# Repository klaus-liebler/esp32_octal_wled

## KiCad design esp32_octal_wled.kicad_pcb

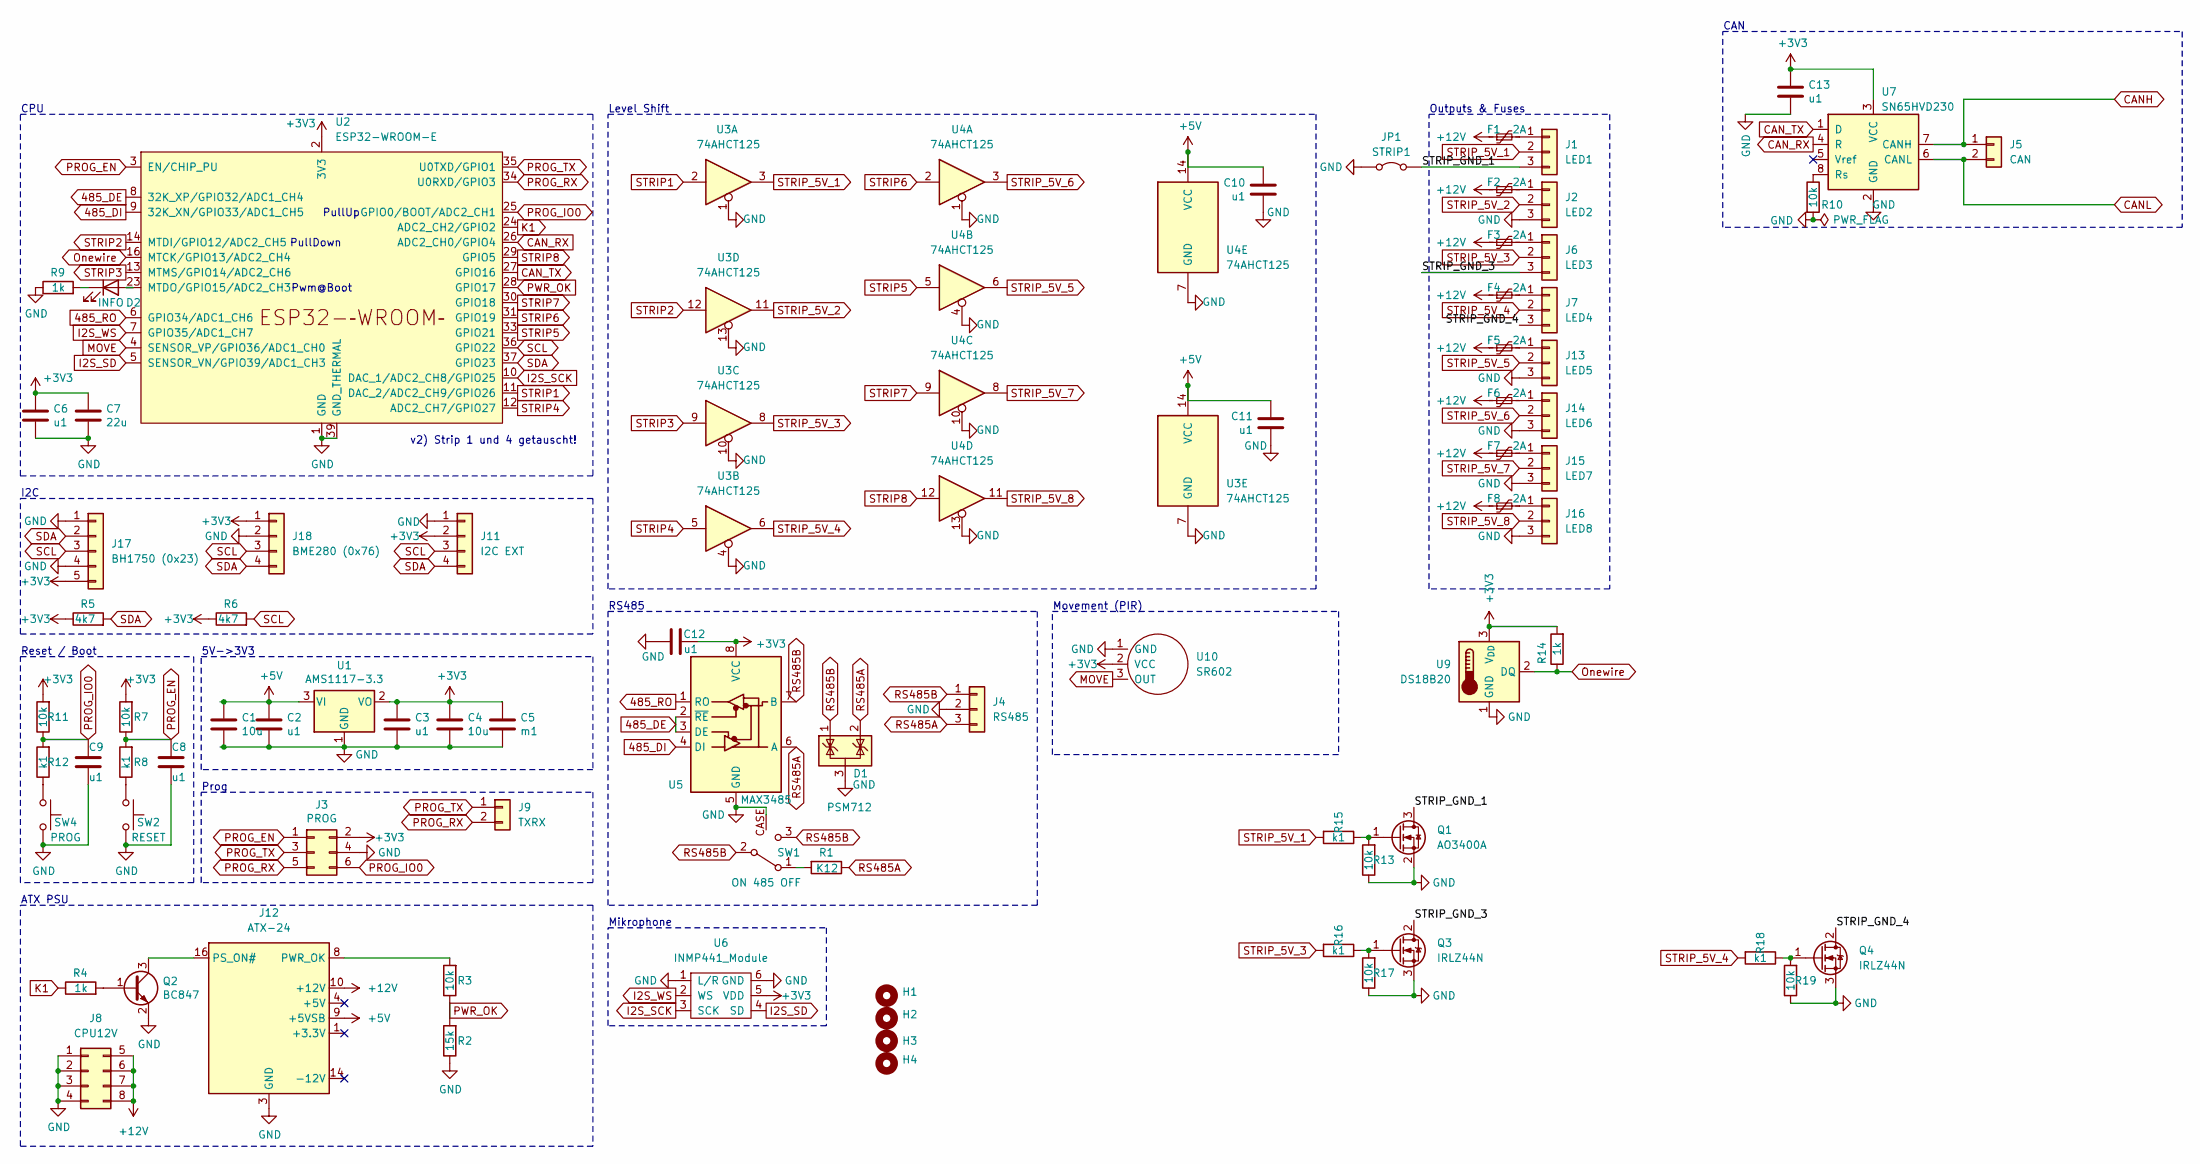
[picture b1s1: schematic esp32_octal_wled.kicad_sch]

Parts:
C1, C4: 10u; C_0805_2012Metric_Pad1.18x1.45mm_HandSolder
C2: u1; C_0805_2012Metric_Pad1.18x1.45mm_HandSolder; JLCPCB C19702
C3, C8, C9, C12, C13: u1; C_0805_2012Metric_Pad1.18x1.45mm_HandSolder
C5: m1; C_1206_3216Metric_Pad1.33x1.80mm_HandSolder; JLCPCB C15008
C6, C10, C11: u1; C_0805_2012Metric_Pad1.18x1.45mm_HandSolder; JLCPCB C1525
C7: 22u; C_0805_2012Metric_Pad1.18x1.45mm_HandSolder; JLCPCB C59461
D1: PSM712; SOT-23_Handsoldering
D2: INFO; LED_0805_2012Metric_Pad1.15x1.40mm_HandSolder
F1, F2, F3, F4, F5, F6, F7, F8: 2A; Fuse_2920_7451Metric_Pad2.10x5.45mm_HandSolder
H1, H2, H3, H4: MountingHole_3.2mm_M3
J1: LED1; PhoenixContact_MC_1,5_3-G-3.5_1x03_P3.50mm_Horizontal_small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
J2: LED2; PhoenixContact_MC_1,5_3-G-3.5_1x03_P3.50mm_Horizontal_small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
J3: PROG; IDC_2x03_P1.27mm_Vertical
J4: RS485; PhoenixContact_MC_1,5_3-G-3.5_1x03_P3.50mm_Horizontal_small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
J5: CAN; PhoenixContact_MCV_1,5_2-G-3.5_1x02_P3.50mm_Vertical
J6: LED3; PhoenixContact_MC_1,5_3-G-3.5_1x03_P3.50mm_Horizontal_small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
J7: LED4; PhoenixContact_MC_1,5_3-G-3.5_1x03_P3.50mm_Horizontal_small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
J8: CPU12V; Molex_Mini-Fit_Jr_5569-08A2_2x04_P4.20mm_Horizontal
J9: TXRX; TestPoint_2Pads_Pitch2.54mm_Drill0.8mm
J11: I2C EXT; JST_XH_S4B-XH-A-1_1x04_P2.50mm_Horizontal_SmallerCourtyard
J12: ATX-24; Molex_Mini-Fit_Jr_5569-24A2_2x12_P4.20mm_Horizontal
J13: LED5; PhoenixContact_MC_1,5_3-G-3.5_1x03_P3.50mm_Horizontal_small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
J14: LED6; PhoenixContact_MC_1,5_3-G-3.5_1x03_P3.50mm_Horizontal_small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
J15: LED7; PhoenixContact_MC_1,5_3-G-3.5_1x03_P3.50mm_Horizontal_small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
J16: LED8; PhoenixContact_MC_1,5_3-G-3.5_1x03_P3.50mm_Horizontal_small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
J17: BH1750 (0x23); PinSocket_1x05_P2.54mm_Vertical
J18: BME280 (0x76); PinSocket_1x04_P2.54mm_Vertical
JP1: STRIP1; SolderJumper-2_P1.3mm_Bridged2Bar_Pad1.0x1.5mm
Q1: AO3400A; SOT-23_Handsoldering
Q2: BC847; SOT-23_Handsoldering
Q3, Q4: IRLZ44N; TO-220-3_Vertical
R1: K12; R_1206_3216Metric_Pad1.30x1.75mm_HandSolder
R2: 15k; R_0805_2012Metric_Pad1.20x1.40mm_HandSolder
R3, R7, R10, R11, R13, R17, R19: 10k; R_0805_2012Metric_Pad1.20x1.40mm_HandSolder
R4, R9, R14: 1k; R_0805_2012Metric_Pad1.20x1.40mm_HandSolder
R5, R6: 4k7; R_0805_2012Metric_Pad1.20x1.40mm_HandSolder
R8, R12, R15, R16, R18: k1; R_0805_2012Metric_Pad1.20x1.40mm_HandSolder
SW1: ON 485 OFF; SW_SPDT_PCM12_handsolder
SW2: RESET; SW_SPST_TL3342_smaller_handsolder
SW4: PROG; SW_SPST_TL3342_smaller_handsolder
U1: AMS1117-3.3; SOT-223-3_TabPin2
U2: ESP32-WROOM-E; ESP32-WROOM-32_HANDSOLDER
U3, U4: 74AHCT125; SOIC-14_3.9x8.7mm_P1.27mm_handsolder
U5: MAX3485; SOIC-8_3.9x4.9mm_P1.27mm_handsolder
U6: INMP441_Module
U7: SN65HVD230; SOIC-8_3.9x4.9mm_P1.27mm_handsolder
U9: DS18B20; TO-92L_HandSolder
U10: SR602; PIR_Sensor_SR602

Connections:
485_DE: U2.8 (32K_XP/GPIO32/ADC1_CH4), U5.2 (~RE), U5.3 (DE)
485_DI: U2.9 (32K_XN/GPIO33/ADC1_CH5), U5.4 (DI)
485_RO: U2.6 (GPIO34/ADC1_CH6), U5.1 (RO)
+3V3: C3.1, C4.1, C5.1, C6.1, C7.1, C12.1, C13.1, J3.2, J11.2, J17.5, J18.1, R5.1, R6.1, R7.2, R11.2, R14.2, U1.2 (VO), U2.2 (3V3), U5.8 (VCC), U6.5 (VDD), U7.3 (VCC), U9.3 (V_{DD}), U10.2 (VCC)
+5V: C1.1, C2.1, C10.1, C11.1, J12.9 (+5VSB), U1.3 (VI), U3.14 (VCC), U4.14 (VCC)
+12V: F1.1, F2.1, F3.1, F4.1, F5.1, F6.1, F7.1, F8.1, J8.5, J8.6, J8.7, J8.8, J12.10 (+12V), J12.11 (+12V)
/STRIP_GND_1: J1.3, JP1.2 (B), Q1.3 (D)
/STRIP_GND_3: J6.3, Q3.2 (D)
/STRIP_GND_4: J7.3, Q4.2 (D)
CANH: J5.1, U7.7 (CANH)
CANL: J5.2, U7.6 (CANL)
CAN_RX: U2.26 (ADC2_CH0/GPIO4), U7.4 (R)
CAN_TX: U2.27 (GPIO16), U7.1 (D)
GND: C1.2, C2.2, C3.2, C4.2, C5.2, C6.2, C7.2, C8.2, C9.2, C10.2, C11.2, C12.2, C13.2, D1.3 (A), J2.3, J3.4, J4.2, J8.1, J8.2, J8.3, J8.4, J11.1, J12.3 (GND), J12.5 (GND), J12.7 (GND), J12.15 (GND), J12.17 (GND), J12.18 (GND), J12.19 (GND), J12.24 (GND), J13.3, J14.3, J15.3, J16.3, J17.1, J17.4, J18.2, JP1.1 (A), Q1.2 (S), Q2.2 (E), Q3.3 (S), Q4.3 (S), R2.1, R9.1, R10.2, R13.1, R17.1, R19.1, SW1.CASE, SW2.2, SW4.2, U1.1 (GND), U2.1 (GND), U2.15 (GND), U2.38 (GND), U2.39 (GND_THERMAL), U3.1, U3.4, U3.7 (GND), U3.10, U3.13, U4.1, U4.4, U4.7 (GND), U4.10, U4.13, U5.5 (GND), U6.1 (L/R), U6.6 (GND), U7.2 (GND), U9.1 (GND), U10.1 (GND)
I2S_SCK: U2.10 (DAC_1/ADC2_CH8/GPIO25), U6.3 (SCK)
I2S_SD: U2.5 (SENSOR_VN/GPIO39/ADC1_CH3), U6.4 (SD)
I2S_WS: U2.7 (GPIO35/ADC1_CH7), U6.2 (WS)
K1: R4.1, U2.24 (ADC2_CH2/GPIO2)
MOVE: U2.4 (SENSOR_VP/GPIO36/ADC1_CH0), U10.3 (OUT)
unnamed: D2.2 (A), U2.23 (MTDO/GPIO15/ADC2_CH3)
unnamed: D2.1 (K), R9.2
unnamed: F1.2, J1.1
unnamed: F2.2, J2.1
unnamed: F3.2, J6.1
unnamed: F4.2, J7.1
unnamed: J12.16 (PS_ON#), Q2.3 (C)
unnamed: J12.8 (PWR_OK), R3.2
unnamed: F5.2, J13.1
unnamed: F6.2, J14.1
unnamed: F7.2, J15.1
unnamed: F8.2, J16.1
unnamed: Q1.1 (G), R13.2, R15.1
unnamed: Q2.1 (B), R4.2
unnamed: Q3.1 (G), R16.1, R17.2
unnamed: Q4.1 (G), R18.1, R19.2
unnamed: R8.1, SW2.1
unnamed: R12.1, SW4.1
unnamed: R1.2, SW1.1 (A)
unnamed: R10.1, U7.8 (Rs)
Onewire: R14.1, U2.16 (MTCK/GPIO13/ADC2_CH4), U9.2 (DQ)
PROG_EN: C8.1, J3.1, R7.1, R8.2, U2.3 (EN/CHIP_PU)
PROG_IO0: C9.1, J3.6, R11.1, R12.2, U2.25 (GPIO0/BOOT/ADC2_CH1)
PROG_RX: J3.5, J9.2, U2.34 (U0RXD/GPIO3)
PROG_TX: J3.3, J9.1, U2.35 (U0TXD/GPIO1)
PWR_OK: R2.2, R3.1, U2.28 (GPIO17)
RS485A: D1.2 (K), J4.3, R1.1, U5.6 (A)
RS485B: D1.1 (K), J4.1, SW1.2 (B), SW1.3 (C), U5.7 (B)
SCL: J11.3, J17.3, J18.3, R6.2, U2.36 (GPIO22)
SDA: J11.4, J17.2, J18.4, R5.2, U2.37 (GPIO23)
STRIP1: U2.11 (DAC_2/ADC2_CH9/GPIO26), U3.2
STRIP2: U2.14 (MTDI/GPIO12/ADC2_CH5), U3.12
STRIP3: U2.13 (MTMS/GPIO14/ADC2_CH6), U3.9
STRIP4: U2.12 (ADC2_CH7/GPIO27), U3.5
STRIP5: U2.33 (GPIO21), U4.5
STRIP6: U2.31 (GPIO19), U4.2
STRIP7: U2.30 (GPIO18), U4.9
STRIP8: U2.29 (GPIO5), U4.12
STRIP_5V_1: J1.2, R15.2, U3.3
STRIP_5V_2: J2.2, U3.11
STRIP_5V_3: J6.2, R16.2, U3.8
STRIP_5V_4: J7.2, R18.2, U3.6
STRIP_5V_5: J13.2, U4.6
STRIP_5V_6: J14.2, U4.3
STRIP_5V_7: J15.2, U4.8
STRIP_5V_8: J16.2, U4.11

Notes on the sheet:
v2) Strip 1 und 4 getauscht!
Movement (PIR)
CPU
Outputs & Fuses
CAN
Mikrophone
Level Shift
Prog
PullDown
Pwm@Boot
Reset / Boot
PullUp
ATX PSU
5V->3V3
I2C
RS485

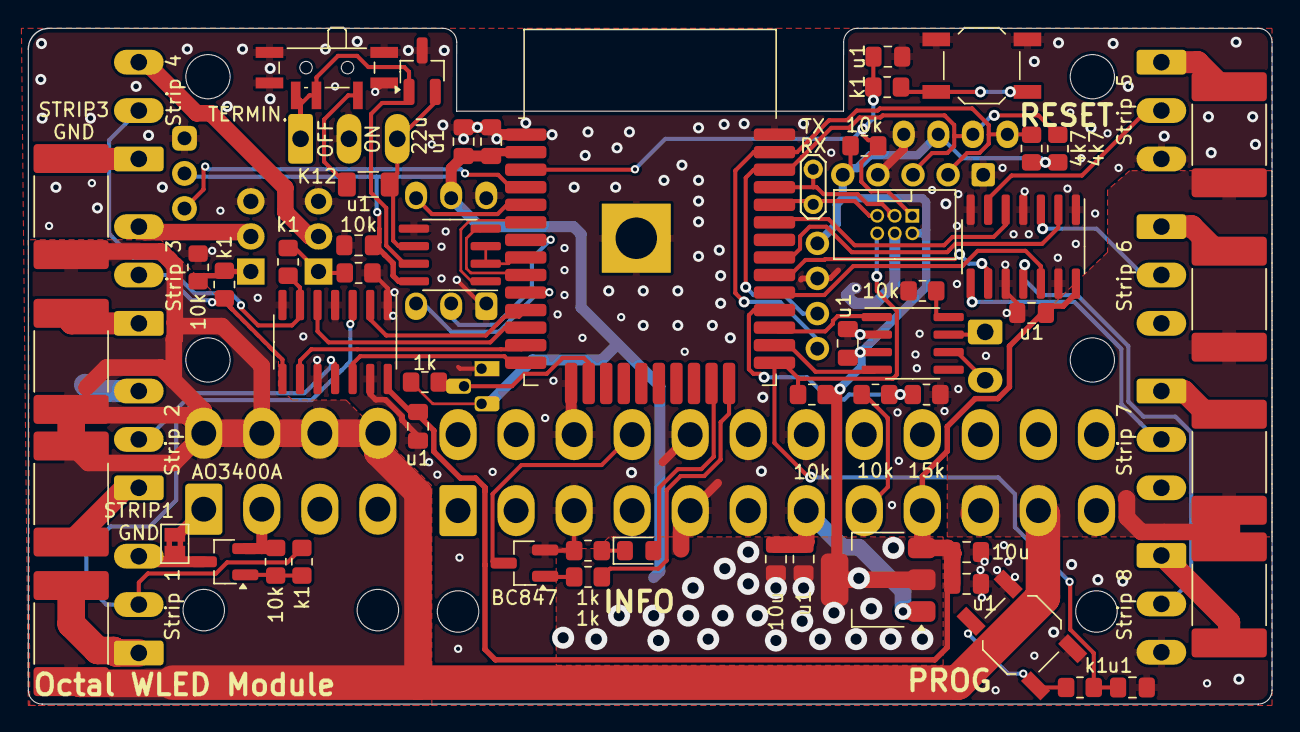
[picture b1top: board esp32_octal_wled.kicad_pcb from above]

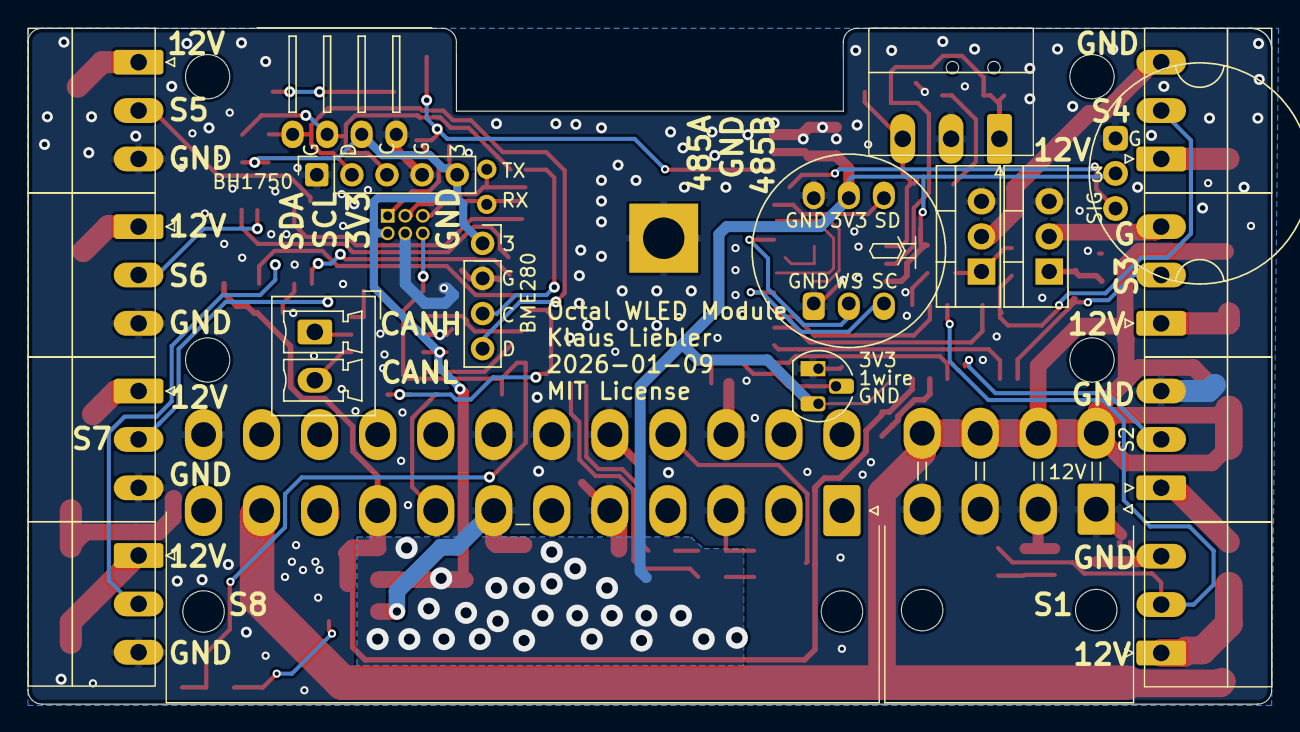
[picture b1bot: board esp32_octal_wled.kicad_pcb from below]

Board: 2 copper layers, 90.0 x 48.9 mm, 79 parts (20 on the bottom side), 65 nets.

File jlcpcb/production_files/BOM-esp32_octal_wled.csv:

Comment,Designator,Footprint,LCSC,Quantity
SN65HVD230,U7,SOIC-8_3.9x4.9mm_P1.27mm_handsolder,C12084,1
74AHCT125,"U3,U4",SOIC-14_3.9x8.7mm_P1.27mm_handsolder,C155176,2
u1,"C10,C11,C12,C13,C2,C3,C6,C8,C9",C_0805_2012Metric_Pad1.18x1.45mm_HandSolder,C1711,9
k1,"R12,R15,R16,R18,R8",R_0805_2012Metric_Pad1.20x1.40mm_HandSolder,C17408,5
10k,"R10,R11,R13,R17,R19,R3,R7",R_0805_2012Metric_Pad1.20x1.40mm_HandSolder,C17414,7
1k,"R14,R4,R9",R_0805_2012Metric_Pad1.20x1.40mm_HandSolder,C17513,3
4k7,"R5,R6",R_0805_2012Metric_Pad1.20x1.40mm_HandSolder,C17673,2
2A,"F1,F2,F3,F4,F5,F6,F7,F8",Fuse_2920_7451Metric_Pad2.10x5.45mm_HandSolder,C19078744,8
RESET,"SW2,SW4",SW_SPST_TL3342_smaller_handsolder,C318884,2
BC847,Q2,SOT-23_Handsoldering,C41371422,1
22u,C7,C_0805_2012Metric_Pad1.18x1.45mm_HandSolder,C5674,1
10u,"C1,C4",C_0805_2012Metric_Pad1.18x1.45mm_HandSolder,C6119888,2
AMS1117-3.3,U1,SOT-223-3_TabPin2,C6186,1
ESP32-WROOM-E,U2,ESP32-WROOM-32_HANDSOLDER,C701342,1
INFO,D2,LED_0805_2012Metric_Pad1.15x1.40mm_HandSolder,C84261,1
MAX3485,U5,SOIC-8_3.9x4.9mm_P1.27mm_handsolder,C8963,1

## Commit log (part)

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2024-11-15 As ordered at JLCPCB
2024-12-15 Fixes
2024-12-19 INMP441
2025-01-09 Two layer PCB, other PCB format
2025-01-14 Various
2025-01-14 OctalWLED as ordered @ JLCPCB
2025-02-04 Minor updates
2025-04-25 Updated to KiCad 9
2025-12-01 Minor fixes
2026-01-29 New Version as ordered @ JLCPCB

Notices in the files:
esp32_octal_wled.kicad_pcb:
MIT License
